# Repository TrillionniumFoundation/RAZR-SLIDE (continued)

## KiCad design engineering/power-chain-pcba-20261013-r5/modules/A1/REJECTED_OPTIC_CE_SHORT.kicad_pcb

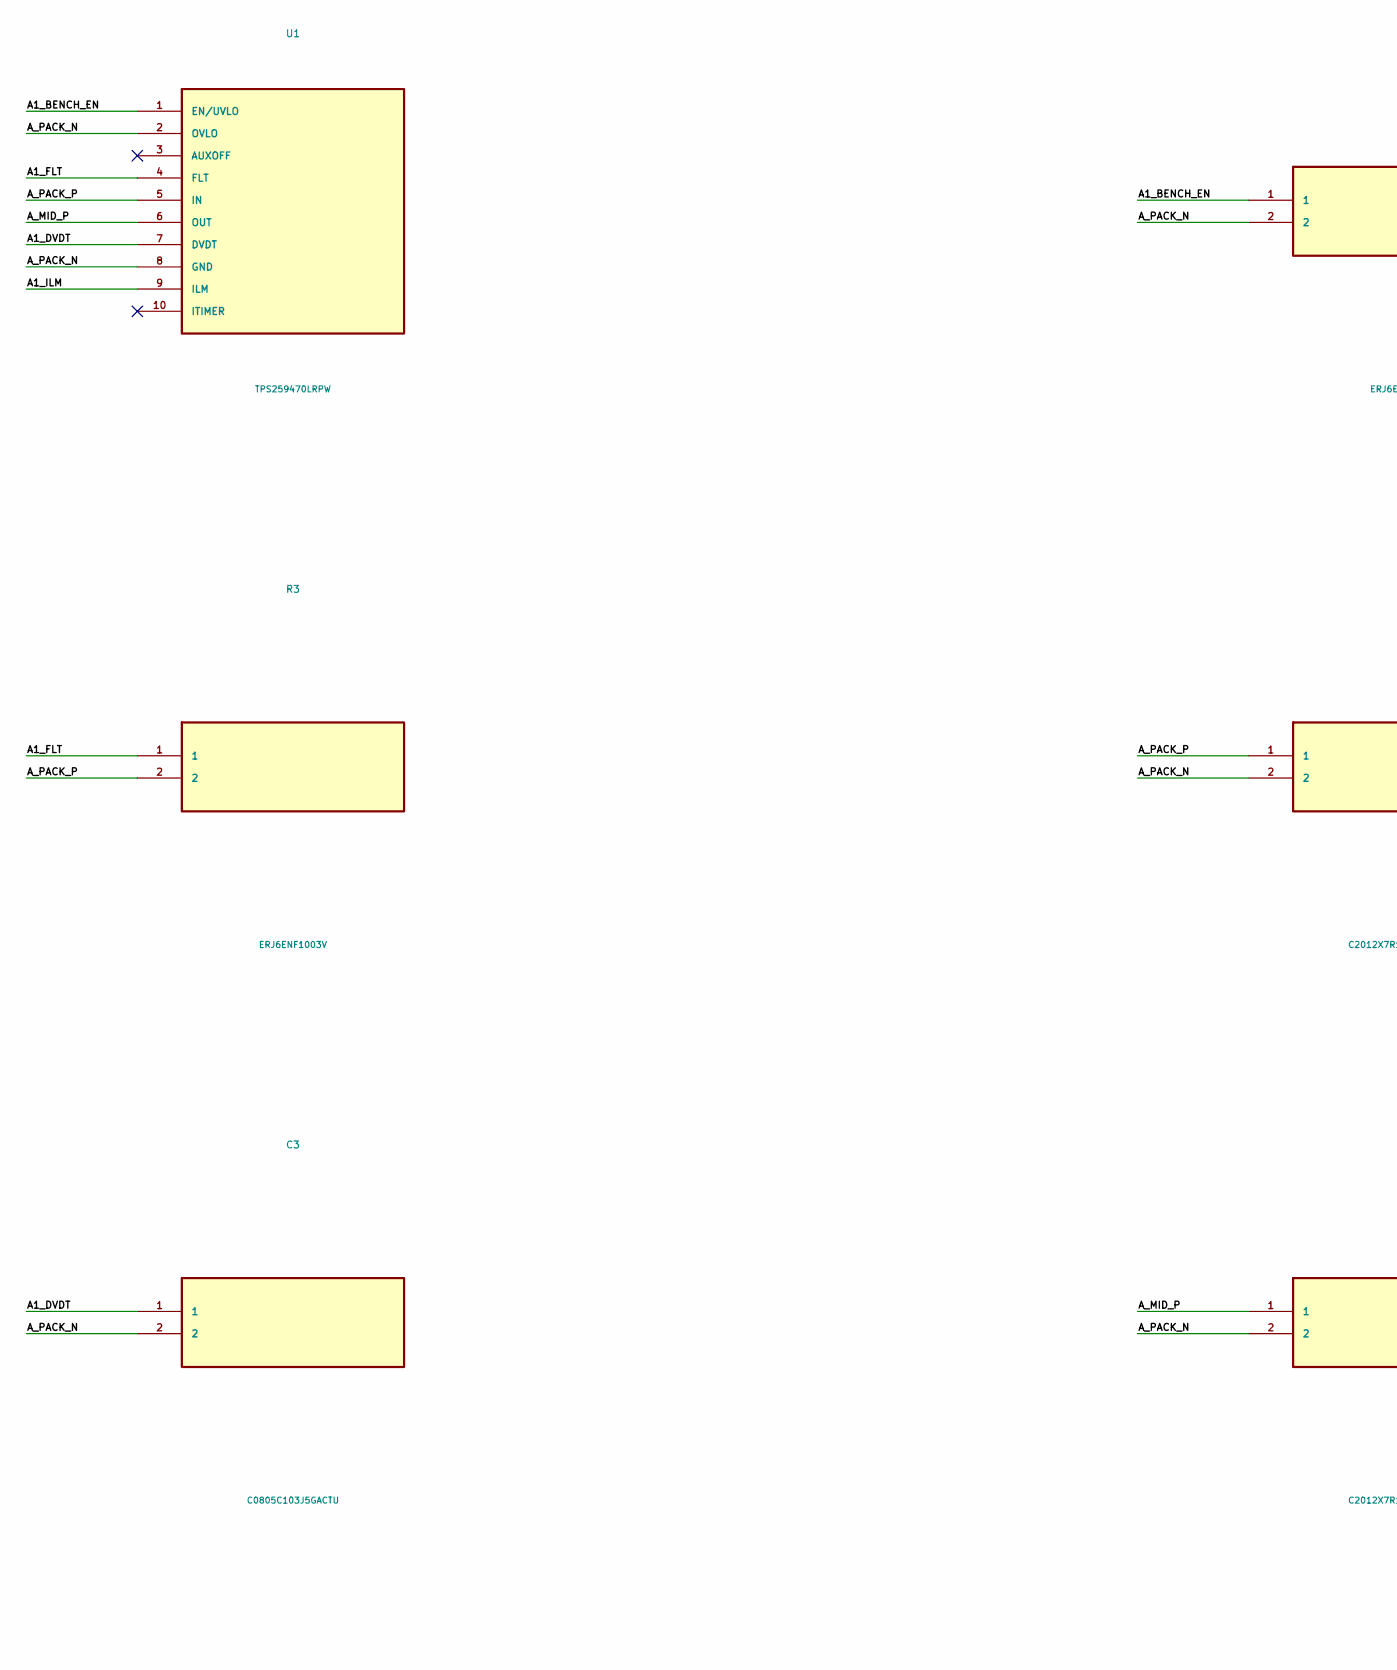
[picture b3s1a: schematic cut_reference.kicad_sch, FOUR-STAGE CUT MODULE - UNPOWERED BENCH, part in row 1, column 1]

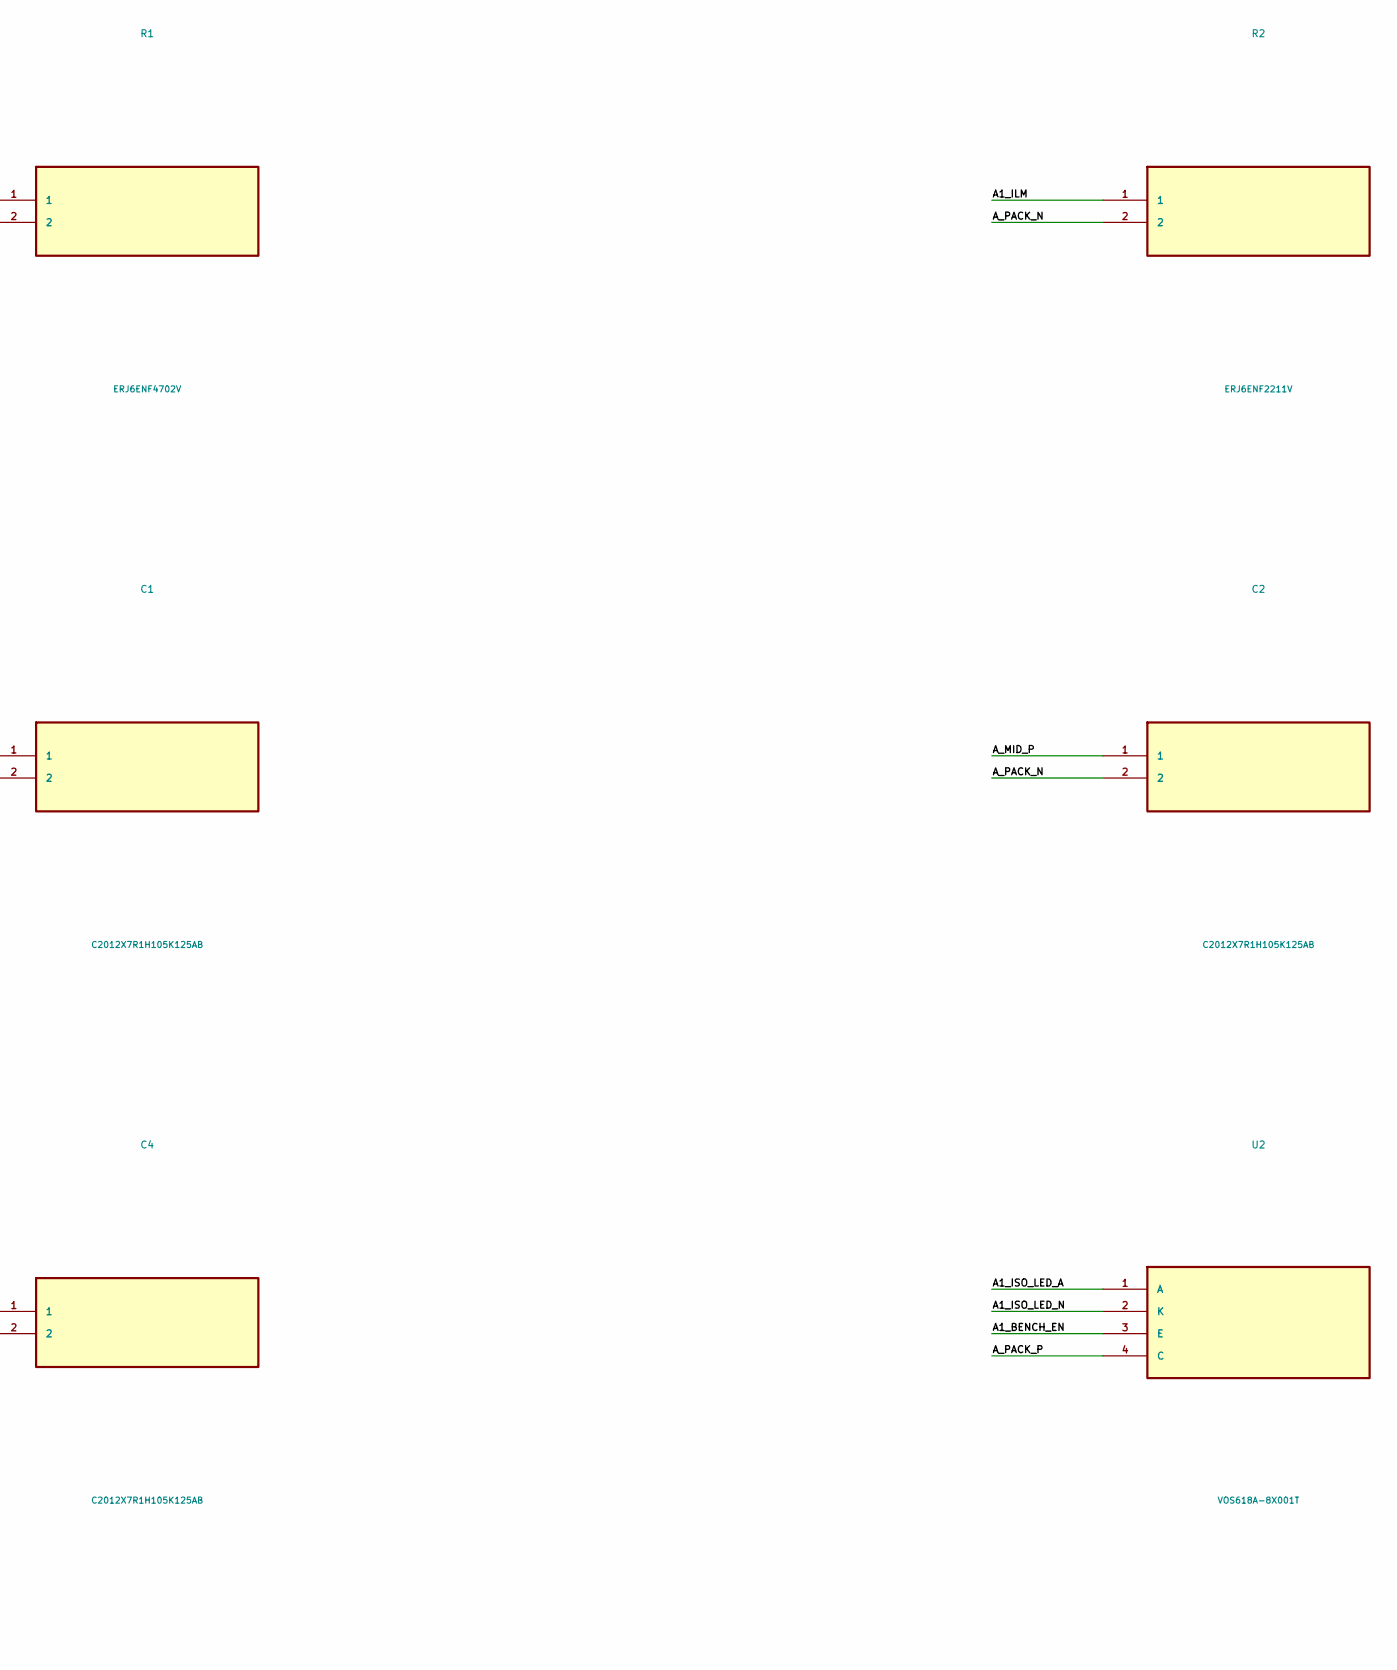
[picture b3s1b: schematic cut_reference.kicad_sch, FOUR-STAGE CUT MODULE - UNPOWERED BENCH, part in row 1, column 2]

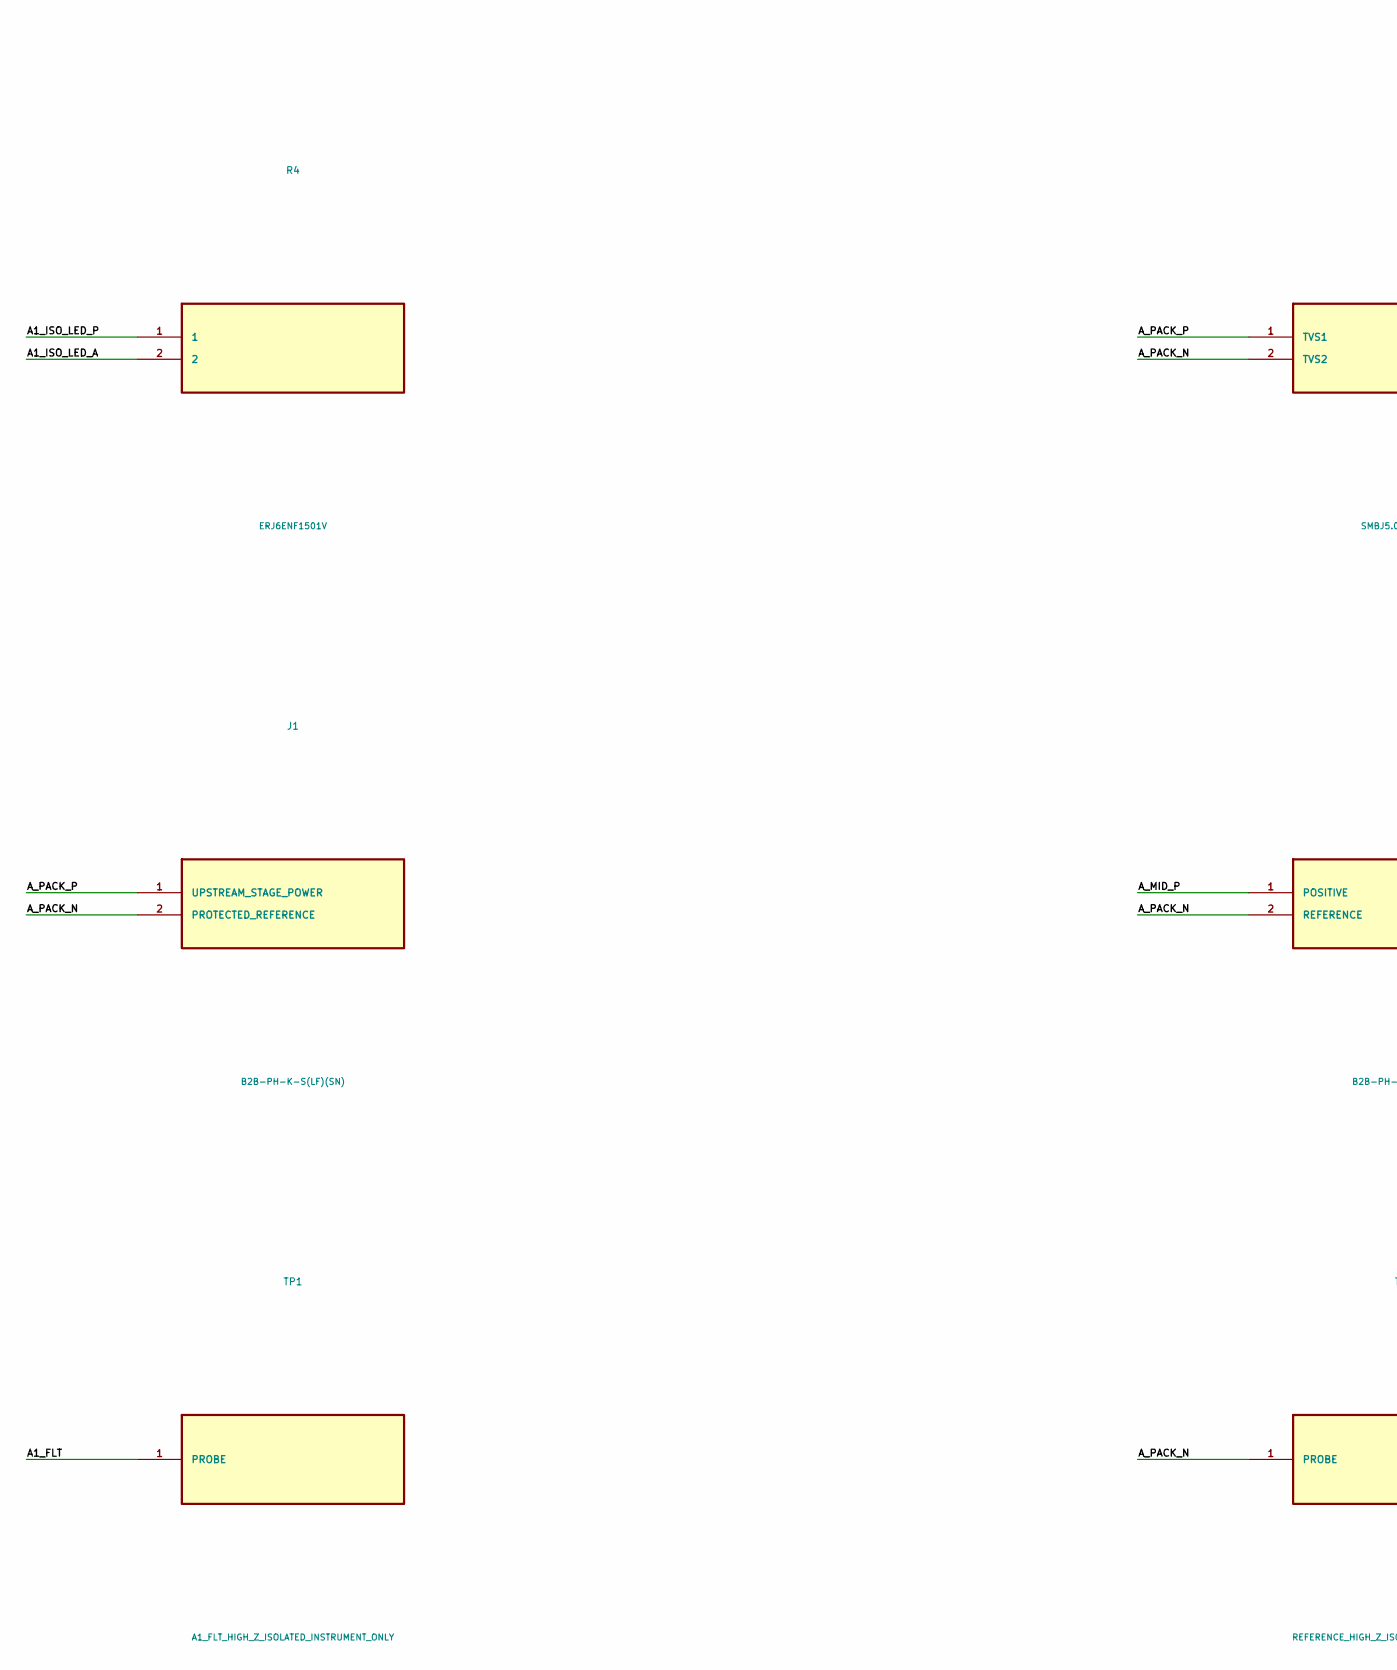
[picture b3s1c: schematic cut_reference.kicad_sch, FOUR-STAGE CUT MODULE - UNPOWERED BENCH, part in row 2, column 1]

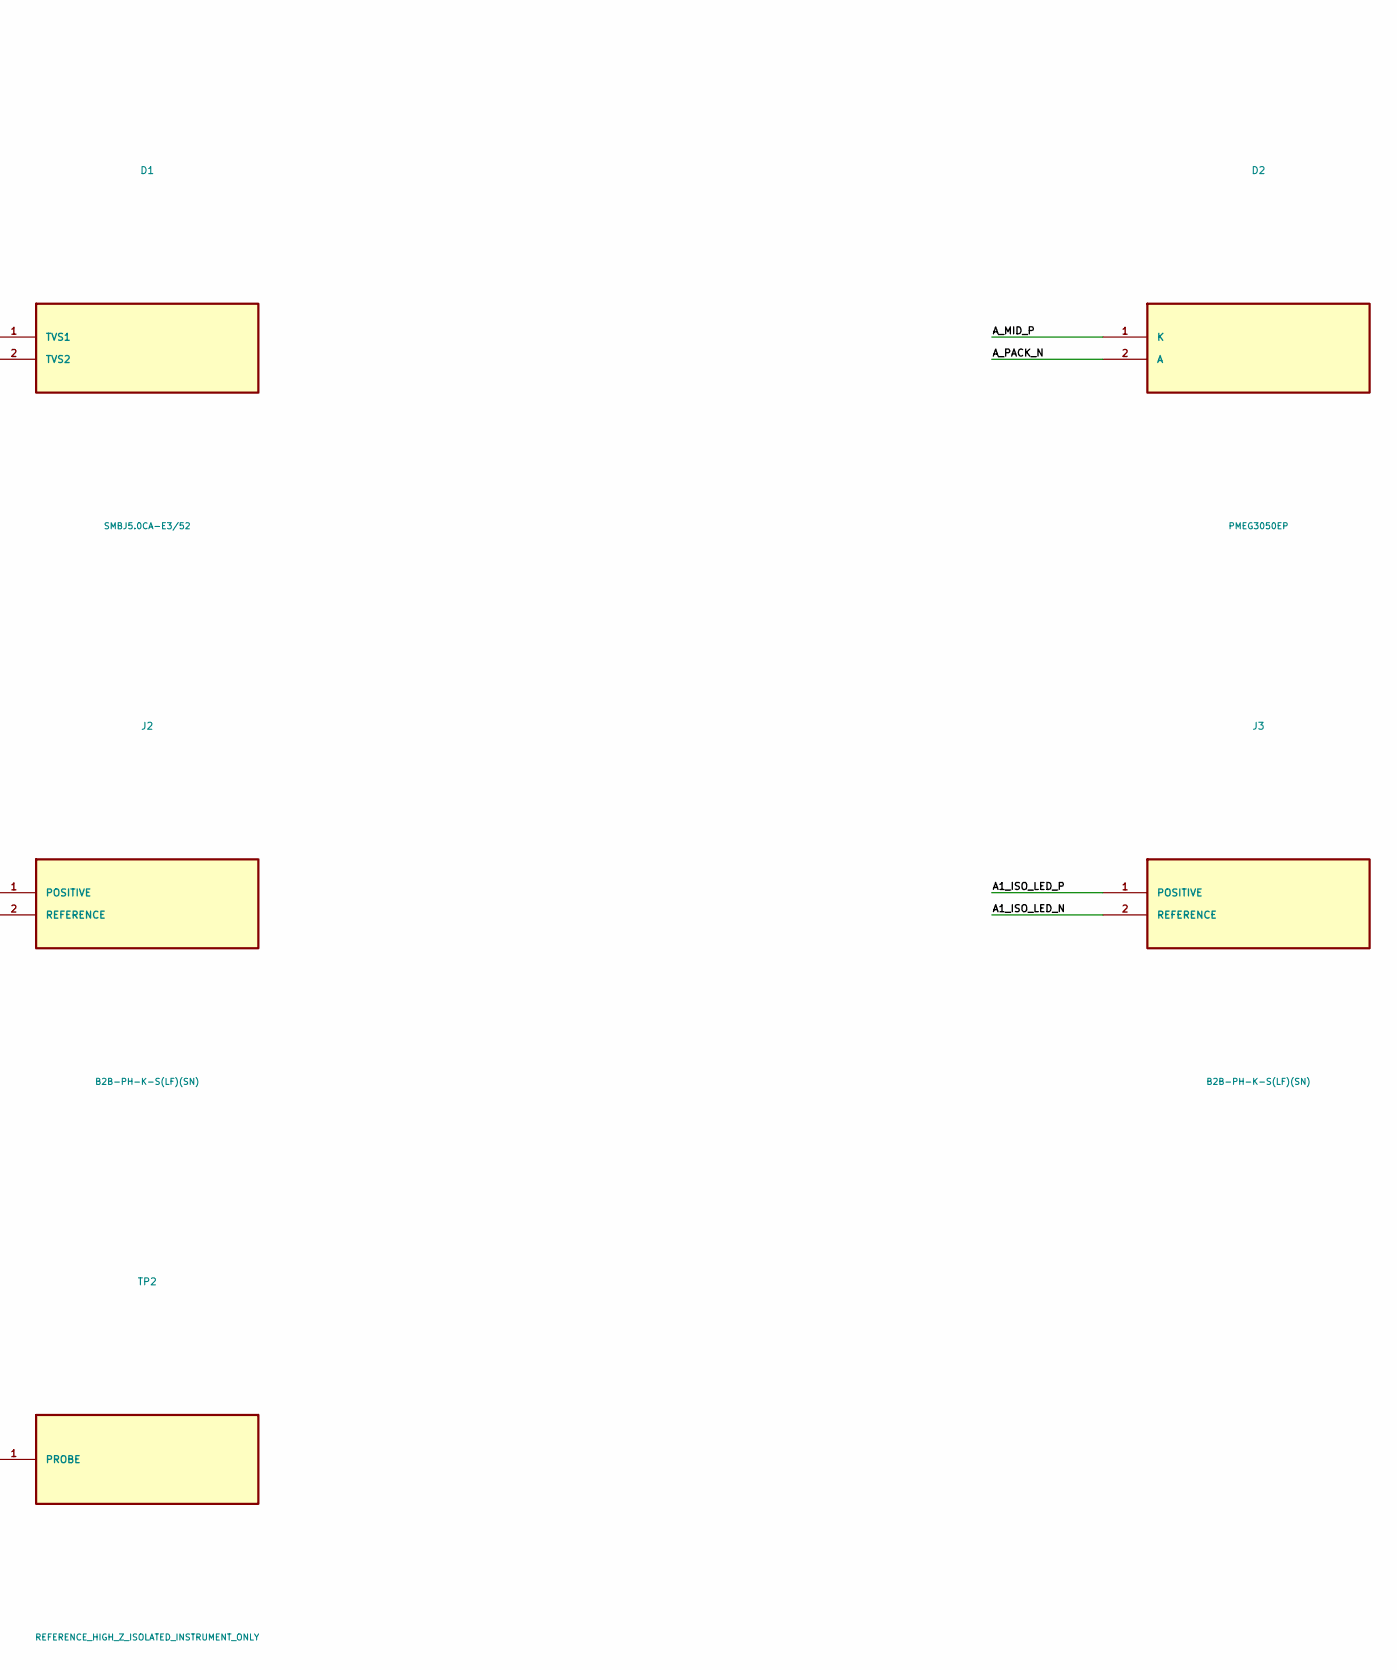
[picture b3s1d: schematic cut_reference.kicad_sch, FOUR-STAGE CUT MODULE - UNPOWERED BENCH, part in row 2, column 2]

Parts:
C1, C2, C4: C2012X7R1H105K125AB; Passive_0805_BENCH
C3: C0805C103J5GACTU; Passive_0805_BENCH
D1: SMBJ5.0CA-E3/52; SMB_OWNED_NOMINAL
D2: PMEG3050EP; SOD128_OWNED_NOMINAL
J1: B2B-PH-K-S(LF)(SN); PH2_OWNED_VERTICAL_IN
J2: B2B-PH-K-S(LF)(SN); PH2_OWNED_VERTICAL_OUT
J3: B2B-PH-K-S(LF)(SN); PH2_OWNED_HORIZONTAL
R1: ERJ6ENF4702V; Passive_0805_Vertical_BENCH
R2: ERJ6ENF2211V; Passive_0805_BENCH
R3: ERJ6ENF1003V; Passive_0805_BENCH
R4: ERJ6ENF1501V; Passive_0805_BENCH
TP1: A1_FLT_HIGH_Z_ISOLATED_INSTRUMENT_ONLY; Probe_1p8mm
TP2: REFERENCE_HIGH_Z_ISOLATED_INSTRUMENT_ONLY; Probe_1p8mm
U1: TPS259470LRPW; RPW0010A_OWNED_NOMINAL
U2: VOS618A-8X001T; VOS618A_OWNED_DATASHEET

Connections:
A1_BENCH_EN: R1.1, U1.1 (EN/UVLO), U2.3 (E)
A1_DVDT: C3.1, U1.7 (DVDT)
A1_FLT: R3.1, TP1.1, U1.4 (FLT)
A1_ILM: R2.1, U1.9 (ILM)
A1_ISO_LED_A: R4.2, U2.1 (A)
A1_ISO_LED_N: J3.2 (REFERENCE), U2.2 (K)
A1_ISO_LED_P: J3.1 (POSITIVE), R4.1
A_MID_P: C2.1, C4.1, D2.1 (K), J2.1 (POSITIVE), U1.6 (OUT)
A_PACK_N: C1.2, C2.2, C3.2, C4.2, D1.2 (TVS2), D2.2 (A), J1.2 (PROTECTED_REFERENCE), J2.2 (REFERENCE), R1.2, R2.2, TP2.1, U1.2 (OVLO), U1.8 (GND)
A_PACK_P: C1.1, D1.1 (TVS1), J1.1 (UPSTREAM_STAGE_POWER), R3.2, U1.5 (IN), U2.4 (C)

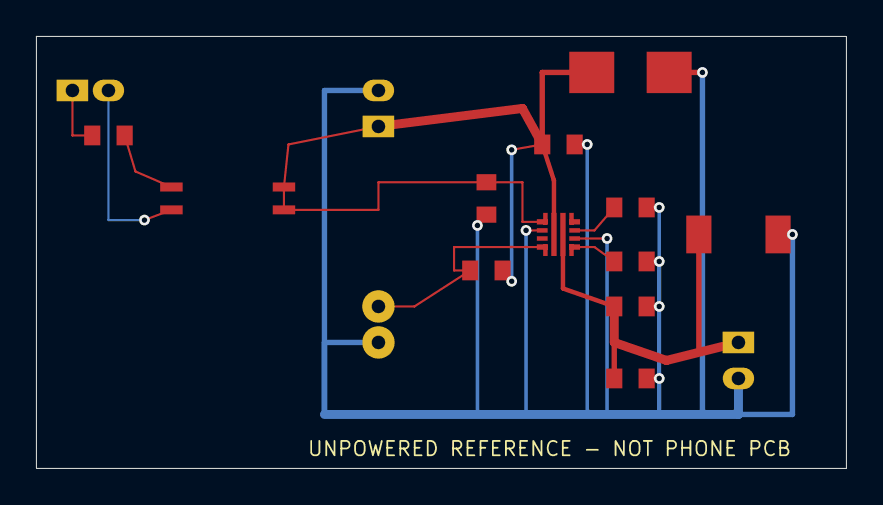
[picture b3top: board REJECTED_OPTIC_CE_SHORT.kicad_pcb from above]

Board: 2 copper layers, 45.0 x 24.0 mm, 17 parts (0 on the bottom side), 10 nets.
